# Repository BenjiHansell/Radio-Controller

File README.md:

# Radio-Controller
A 3D printed radio controller with a custom PCB and firmware.  Click on one of the folders above for more details.

Video:

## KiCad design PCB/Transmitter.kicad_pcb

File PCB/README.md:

# PCB

The PCB is designed using KiCAD.  The schematic is based around that of the Arduino Pro Mini, with an ATmega328P clocked at 16 MHz on a 5V supply.  There are pin headers for connecting an SPI NRF24L01+ radio module (which has a dedicated 3.3V supply), an I2C LCD display, some LEDs, switches, analog sticks and a UART programmer.  There is a potential divider for reading the battery voltage.

## Order boards

I ordered my boards at OSH Park https://oshpark.com/shared_projects/BLpBqENQ

## Room for improvement

This PCB is the first iteration, with a few imperfections.  If I order more copies I will make the following minor modifications:
* A rectangular (rather than square) form factor would allow for more comfortable vertical mounting inside the radio controller
* The rotary encoder needs its own header with power, ground and 3 digital inputs
* PD0, PD1 and PD2 could be broken out for use with additional aux switches

## Long term improvements

The following major features could also be added later:
* A more powerful (yet inexpensive) MCU, such as the STM32F103C8T6
* 1S Li-Ion recharge and boost circuitry (via a USB-B or USB-C port)
* On-board programming (via the same USB port)

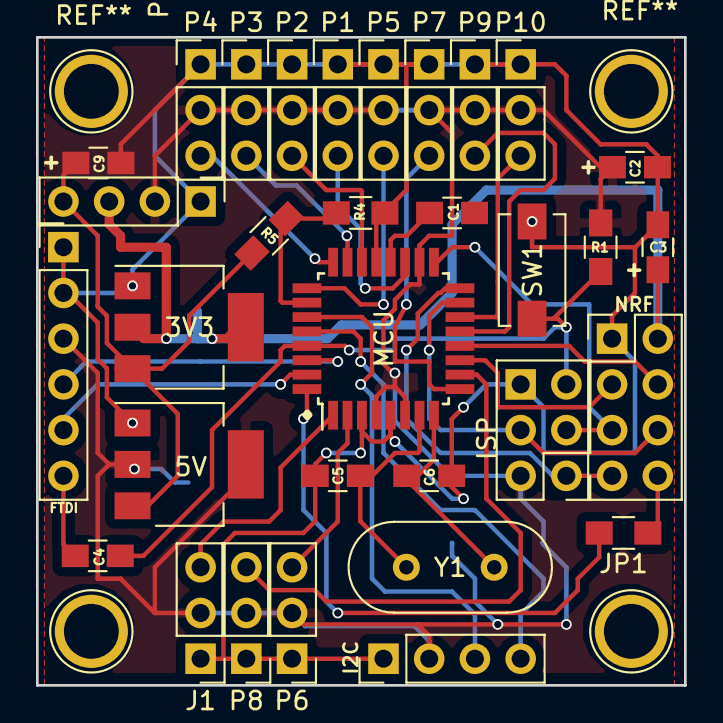
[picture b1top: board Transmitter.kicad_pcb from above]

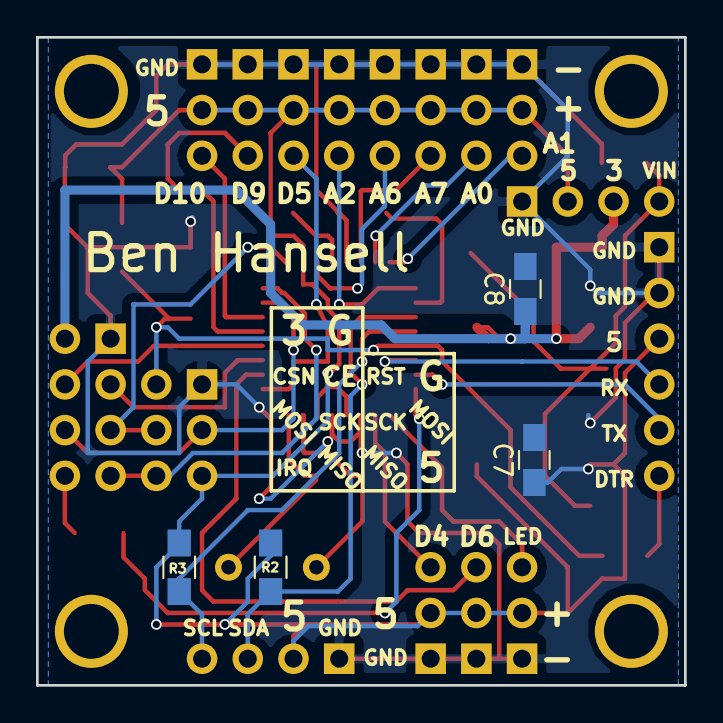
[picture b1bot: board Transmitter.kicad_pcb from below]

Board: 2 copper layers, 36.0 x 36.0 mm, 36 parts (4 on the bottom side), 32 nets.

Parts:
3V3: LM1117-3.3; SOT-223-3Lead_TabPin2
5V: LM1117-5.0; SOT-223-3Lead_TabPin2
C1, C2, C3, C4, C5, C6: C; C_0805_HandSoldering
C7, C8, C9: CP; C_0805_HandSoldering
FTDI: CONN_01X06; Pin_Header_Straight_1x06_Pitch2.54mm
I2C: CONN_01X04; Pin_Header_Straight_1x04_Pitch2.54mm
ISP: AVR-ISP-6; Pin_Header_Straight_2x03_Pitch2.54mm
J1: CONN_01X03; Pin_Header_Straight_1x03_Pitch2.54mm
JP1: Jumper_NO_Small; R_0805_HandSoldering
MCU: ATMEGA328P-A; TQFP-32_7x7mm_Pitch0.8mm
NRF: CONN_02X04; Pin_Header_Straight_2x04_Pitch2.54mm
P1, P2, P3, P4, P5, P6, P7, P8, P9, P10: CONN_01X03; Pin_Header_Straight_1x03_Pitch2.54mm
P12: CONN_01X04; Pin_Header_Straight_1x04_Pitch2.54mm
R1, R2, R3, R4, R5: R; R_0805_HandSoldering
SW1: SW_PUSH; SW_SPST_EVQPE1
Y1: Crystal; Crystal_HC49-U_Vertical

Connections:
+3V3: 3V3.2, C3.2, C8.1, NRF.2, P12.3
+5V: 5V.2, C2.2, C7.1, FTDI.3, I2C.2, ISP.2, J1.2, MCU.4, MCU.6, MCU.18, P1.2, P2.2, P3.2, P4.2, P5.2, P6.2, P7.2, P8.2, P9.2, P10.2, P12.2, R1.1, R2.2, R3.1
/A0: MCU.23, P3.3
/A1: MCU.24, P4.3
/A2: MCU.25, P5.3
/A6: MCU.19, P1.3
/A7: MCU.22, P2.3
/BADC: MCU.26, R4.1, R5.2
/CE: MCU.11, NRF.3
/CSN: MCU.12, NRF.4
/D4: MCU.2, P6.3
/D5: MCU.9, P7.3
/D6: MCU.10, P8.3
/D9: MCU.13, P9.3
/D10: MCU.14, P10.3
/DTR: C4.1, FTDI.6
/IRQ: JP1.2, MCU.32
/LED: J1.3, MCU.1
/MISO: ISP.1, MCU.16, NRF.7
/MOSI: ISP.4, MCU.15, NRF.6
/RST: C4.2, ISP.5, MCU.29, R1.2, SW1.1
/RXD: FTDI.4, MCU.30
/SCK: ISP.3, MCU.17, NRF.5
/SCL: I2C.4, MCU.28, R3.2
/SDA: I2C.3, MCU.27, R2.1
/TXD: FTDI.5, MCU.31
/VIN: 3V3.3, 5V.3, C9.1, P12.4, R5.1
GND: 3V3.1, 5V.1, C1.2, C2.1, C3.1, C5.1, C6.1, C7.2, C8.2, C9.2, FTDI.1, FTDI.2, I2C.1, ISP.6, J1.1, MCU.3, MCU.5, MCU.21, NRF.1, P1.1, P2.1, P3.1, P4.1, P5.1, P6.1, P7.1, P8.1, P9.1, P10.1, P12.1, R4.2, SW1.2
unnamed: C1.1, MCU.20
unnamed: C5.2, MCU.7, Y1.1
unnamed: C6.2, MCU.8, Y1.2
unnamed: JP1.1, NRF.8

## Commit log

2017-09-28 Added photo
